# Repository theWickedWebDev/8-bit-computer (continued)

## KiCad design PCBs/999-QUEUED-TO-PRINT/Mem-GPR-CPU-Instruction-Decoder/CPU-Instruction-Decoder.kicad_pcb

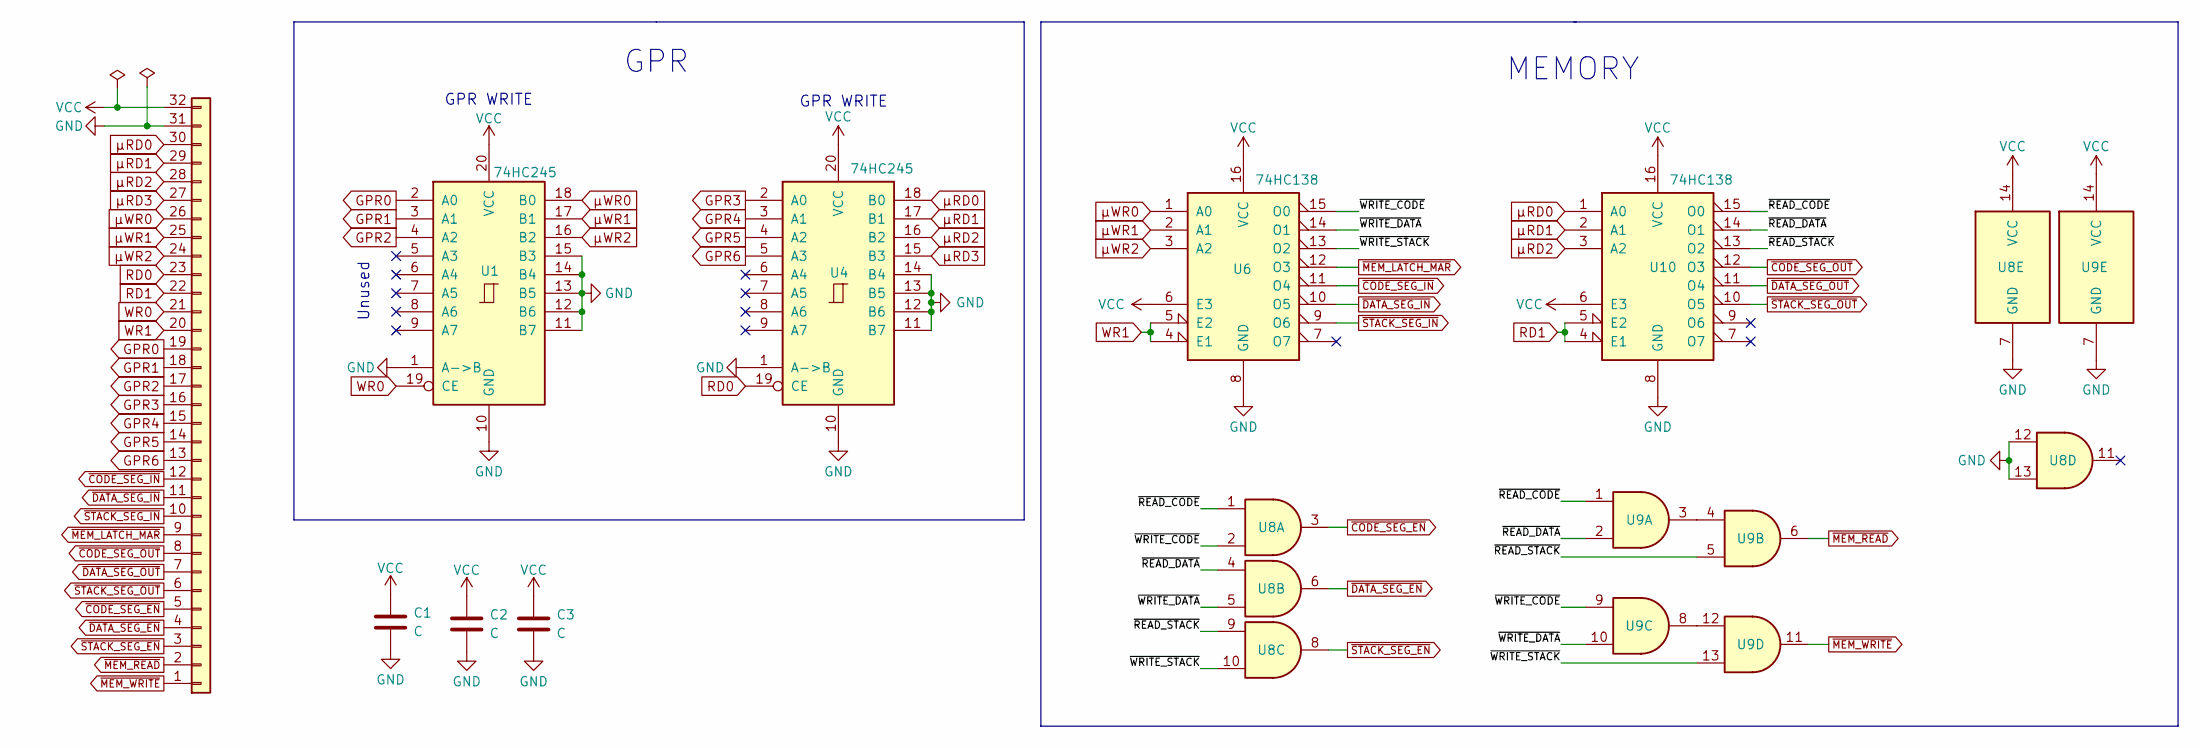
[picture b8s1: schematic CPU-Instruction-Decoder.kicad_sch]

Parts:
C1, C2, C3: C; C_0805_2012Metric
J1: Conn_01x32; PinHeader_1x32_P2.54mm_Horizontal
U1, U4: 74HC245; SOIC-20W_7.5x12.8mm_P1.27mm
U6, U10: 74HC138; SOIC-16_3.9x9.9mm_P1.27mm
U8, U9: 74HC08; SOIC-14_3.9x8.7mm_P1.27mm

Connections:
/~READ_CODE: U8.1, U9.1, U10.15 (O0)
/~READ_DATA: U8.4, U9.2, U10.14 (O1)
/~READ_STACK: U8.9, U9.5, U10.13 (O2)
/~WRITE_CODE: U6.15 (O0), U8.2, U9.9
/~WRITE_DATA: U6.14 (O1), U8.5, U9.10
/~WRITE_STACK: U6.13 (O2), U8.10, U9.13
GND: C1.2, C2.2, C3.2, J1.31, U1.1 (A->B), U1.10 (GND), U1.11 (B7), U1.12 (B6), U1.13 (B5), U1.14 (B4), U1.15 (B3), U4.1 (A->B), U4.10 (GND), U4.11 (B7), U4.12 (B6), U4.13 (B5), U4.14 (B4), U6.8 (GND), U8.7 (GND), U8.12, U8.13, U9.7 (GND), U10.8 (GND)
GPR0: J1.19, U1.2 (A0)
GPR1: J1.18, U1.3 (A1)
GPR2: J1.17, U1.4 (A2)
GPR3: J1.16, U4.2 (A0)
GPR4: J1.15, U4.3 (A1)
GPR5: J1.14, U4.4 (A2)
GPR6: J1.13, U4.5 (A3)
unnamed: U9.3, U9.4
unnamed: U9.8, U9.12
RD0: J1.23, U4.19 (CE)
RD1: J1.22, U10.4 (E1), U10.5 (E2)
VCC: C1.1, C2.1, C3.1, J1.32, U1.20 (VCC), U4.20 (VCC), U6.6 (E3), U6.16 (VCC), U8.14 (VCC), U9.14 (VCC), U10.6 (E3), U10.16 (VCC)
WR0: J1.21, U1.19 (CE)
WR1: J1.20, U6.4 (E1), U6.5 (E2)
~CODE_SEG_EN: J1.5, U8.3
~CODE_SEG_IN: J1.12, U6.11 (O4)
~CODE_SEG_OUT: J1.8, U10.12 (O3)
~DATA_SEG_EN: J1.4, U8.6
~DATA_SEG_IN: J1.11, U6.10 (O5)
~DATA_SEG_OUT: J1.7, U10.11 (O4)
~MEM_LATCH_MAR: J1.9, U6.12 (O3)
~MEM_READ: J1.2, U9.6
~MEM_WRITE: J1.1, U9.11
~STACK_SEG_EN: J1.3, U8.8
~STACK_SEG_IN: J1.10, U6.9 (O6)
~STACK_SEG_OUT: J1.6, U10.10 (O5)
μRD0: J1.30, U4.18 (B0), U10.1 (A0)
μRD1: J1.29, U4.17 (B1), U10.2 (A1)
μRD2: J1.28, U4.16 (B2), U10.3 (A2)
μRD3: J1.27, U4.15 (B3)
μWR0: J1.26, U1.18 (B0), U6.1 (A0)
μWR1: J1.25, U1.17 (B1), U6.2 (A1)
μWR2: J1.24, U1.16 (B2), U6.3 (A2)

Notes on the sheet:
MEMORY
GPR
GPR WRITE
Unused

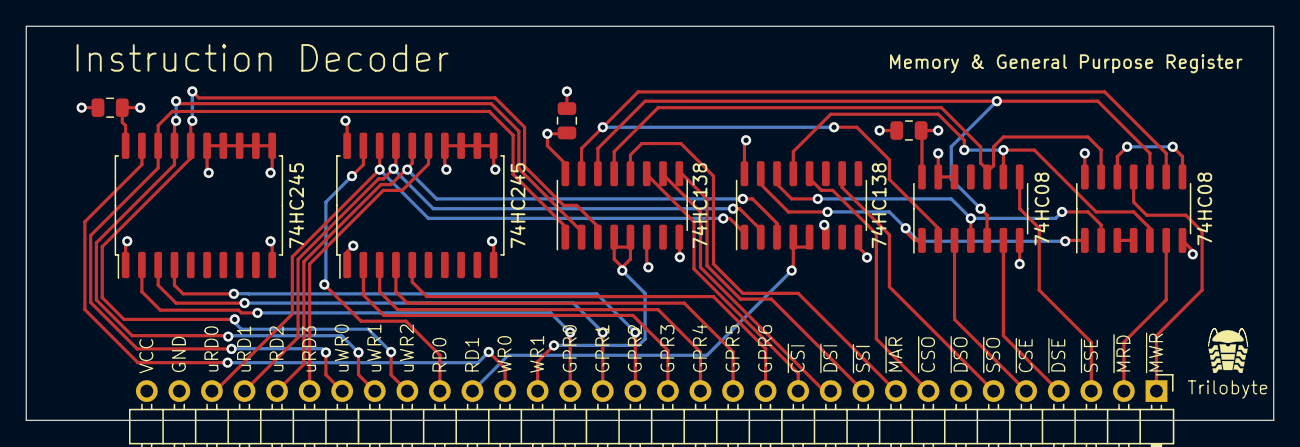
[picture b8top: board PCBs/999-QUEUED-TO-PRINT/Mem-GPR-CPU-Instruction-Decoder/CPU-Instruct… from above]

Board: 4 copper layers, 97.3 x 30.7 mm, 10 parts (0 on the bottom side), 40 nets.

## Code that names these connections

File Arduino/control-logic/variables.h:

#define CPU_CLOCK 12

#define SHIFT_DATA 2
#define SHIFT_CLK 3
#define SHIFT_LATCH 4
#define SHIFT_OE 5

#define BUS_BUFFER_OE 10
#define BUS_BUFFER_DIR_PIN 11

#define BUS0 14
#define BUS1 15
#define BUS2 16
#define BUS3 17
#define BUS4 18
#define BUS5 19
#define BUS6 20
#define BUS7 21


long addressBus = 0x0000;
long dataBus = 0x00;
byte bus = 0x0;

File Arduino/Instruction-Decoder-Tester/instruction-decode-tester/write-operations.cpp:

#define SPR_WR_GROUP    0x3 << 4
#define JCC_WR_GROUP    0x2 << 4
#define MEM_WR_GROUP    0x1 << 4
#define GPR_WR_GROUP    0x0 << 4

// Special Pin
#define INC_PC          0b1 << 7

// CONTROL GROUP 3 (0bx000xxxx)
#define SP_DEC          SPR_WR_GROUP | 0x0
#define SP_INC          SPR_WR_GROUP | 0x1
#define SP_IN           SPR_WR_GROUP | 0x2
#define INST_IN         SPR_WR_GROUP | 0x3
#define A_IN            SPR_WR_GROUP | 0x4
#define B_IN            SPR_WR_GROUP | 0x5
#define PC_DEC          SPR_WR_GROUP | 0x6
// #define FREE         SPR_WR_GROUP | 0x7
// #define FREE         SPR_WR_GROUP | 0x8
#define FLG_IN          SPR_WR_GROUP | 0x9
#define FLG_RESTORE     SPR_WR_GROUP | 0xA
// #define FREE    SPR_WR_GROUP | 0xB .. 0xF

// CONTROL GROUP 2 (0bx001xxxx)
#define JP              JCC_WR_GROUP | 0x0
#define JLE_JNG         JCC_WR_GROUP | 0x1
#define JG_JNLE         JCC_WR_GROUP | 0x2
#define JGE_JNL         JCC_WR_GROUP | 0x3
#define JL_JNGE         JCC_WR_GROUP | 0x4
#define JA_JNBE         JCC_WR_GROUP | 0x5
#define JBE_JNA         JCC_WR_GROUP | 0x6
#define JNB_JAE_JNC     JCC_WR_GROUP | 0x7
#define JB_JNAE_JC      JCC_WR_GROUP | 0x8
#define JNE_JNZ         JCC_WR_GROUP | 0x9
#define JE_JZ           JCC_WR_GROUP | 0xA
#define JNS             JCC_WR_GROUP | 0xB
#define JS              JCC_WR_GROUP | 0xC
#define JNO             JCC_WR_GROUP | 0xD
#define JO              JCC_WR_GROUP | 0xE

// CONTROL GROUP 1 (0bx010xxxx)
#define MEM_CODE_IN     MEM_WR_GROUP | 0x0
#define MEM_DATA_IN     MEM_WR_GROUP | 0x1
#define MEM_STACK_IN    MEM_WR_GROUP | 0x2
#define MAR_IN          MEM_WR_GROUP | 0x3
#define CODE_SEG_IN     MEM_WR_GROUP | 0x4
#define DATA_SEG_IN     MEM_WR_GROUP | 0x5
#define STACK_SEG_IN    MEM_WR_GROUP | 0x6
// #define FREE    MEM_WR_GROUP | 0x7

// CONTROL GROUP 0 (0bx011xxxx)
#define NOP             GPR_WR_GROUP | 0x0
#define C_IN            GPR_WR_GROUP | 0x1
#define D_IN            GPR_WR_GROUP | 0x2
#define S1_IN           GPR_WR_GROUP | 0x3
#define S2_IN           GPR_WR_GROUP | 0x4
#define F               GPR_WR_GROUP | 0x5
#define S3_IN           GPR_WR_GROUP | 0x6

// CONTROL GROUP 4 (0bx100xxxx) - Free Unused (up to 16 more control lines)
// CONTROL GROUP 5 (0bx101xxxx) - Free Unused (up to 16 more control lines)
// CONTROL GROUP 6 (0bx110xxxx) - Free Unused (up to 16 more control lines)
// CONTROL GROUP 7 (0bx111xxxx) - Free Unused (up to 16 more control lines)

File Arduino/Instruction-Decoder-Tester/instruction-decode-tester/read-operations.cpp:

#define SPR_GROUP_OUT           0x4 << 4
#define ALU_GROUP_OUT           0x3 << 4
#define NOT_ALU_GROUP_OUT       0x2 << 4
#define MEM_GROUP_OUT           0x1 << 4
#define GPR_GROUP_OUT           0x0 << 4

// Special Pin
#define RESET_SP                0b1 << 7

// CONTROL GROUP 4 (0bx000xxxx)
#define PC_OUT      SPR_GROUP_OUT | 0x0
#define SP_OUT      SPR_GROUP_OUT | 0x1
#define FLAG_OUT    SPR_GROUP_OUT | 0x2
// #define FREE     SPR_GROUP_OUT | 0x3 .. 0XF // FREE

// CONTROL GROUP 3 (0bx001xxxx)
#define A_OUT       ALU_GROUP_OUT | 0x0
#define ADD_OUT     ALU_GROUP_OUT | 0x1
#define ADC_OUT     ALU_GROUP_OUT | 0x2
#define SUB_OUT     ALU_GROUP_OUT | 0x3
#define SBB_OUT     ALU_GROUP_OUT | 0x4
#define INC_OUT     ALU_GROUP_OUT | 0x5
#define DEC_OUT     ALU_GROUP_OUT | 0x6
#define AND_OUT     ALU_GROUP_OUT | 0x7
#define OR_OUT      ALU_GROUP_OUT | 0x8
#define XOR_OUT     ALU_GROUP_OUT | 0x9
#define SHL_OUT     ALU_GROUP_OUT | 0xA
#define SHR_OUT     ALU_GROUP_OUT | 0xB
#define ASL_OUT     ALU_GROUP_OUT | 0xC
#define ASR_OUT     ALU_GROUP_OUT | 0xD
#define ROR_OUT     ALU_GROUP_OUT | 0xE
#define ROL_OUT     ALU_GROUP_OUT | 0xF

// CONTROL GROUP 2 (0bx010xxxx)
#define NOT_OUT     NOT_ALU_GROUP_OUT | 0x0
#define NADD_OUT    NOT_ALU_GROUP_OUT | 0x1
#define NADC_OUT    NOT_ALU_GROUP_OUT | 0x2
#define NSUB_OUT    NOT_ALU_GROUP_OUT | 0x3
#define NSBB_OUT    NOT_ALU_GROUP_OUT | 0x4
#define NINC_OUT    NOT_ALU_GROUP_OUT | 0x5
#define NDEC_OUT    NOT_ALU_GROUP_OUT | 0x6
#define NAND_OUT    NOT_ALU_GROUP_OUT | 0x7
#define NOR_OUT     NOT_ALU_GROUP_OUT | 0x8
#define XNOR_OUT    NOT_ALU_GROUP_OUT | 0x9
#define NSHL_OUT    NOT_ALU_GROUP_OUT | 0xA
#define NSHR_OUT    NOT_ALU_GROUP_OUT | 0xB
#define NASL_OUT    NOT_ALU_GROUP_OUT | 0xC
#define NASR_OUT    NOT_ALU_GROUP_OUT | 0xD
#define NROR_OUT    NOT_ALU_GROUP_OUT | 0xE
#define NROL_OUT    NOT_ALU_GROUP_OUT | 0xF

// CONTROL GROUP 1 (0bx011xxxx)
#define MEM_CODE_OUT        MEM_GROUP_OUT | 0x0
#define MEM_DATA_OUT        MEM_GROUP_OUT | 0x1
#define MEM_STACK_OUT       MEM_GROUP_OUT | 0x2
#define CODE_SEG_OUT        MEM_GROUP_OUT | 0x3
#define DATA_SEG_OUT        MEM_GROUP_OUT | 0x4
#define STACK_SEG_OUT       MEM_GROUP_OUT | 0x5
// #define MEM_OUT_UNUSED_6    MEM_GROUP_OUT | 0x6
// #define MEM_OUT_UNUSED_6    MEM_GROUP_OUT | 0x7

// CONTROL GROUP 0 (0bx100xxxx)
#define NOP                 GPR_GROUP_OUT | 0x0
#define C_OUT               GPR_GROUP_OUT | 0x1
#define D_OUT               GPR_GROUP_OUT | 0x2
#define S1_OUT              GPR_GROUP_OUT | 0x3
#define S2_OUT              GPR_GROUP_OUT | 0x4
#define S1S2_OUT            GPR_GROUP_OUT | 0x5
#define F_OUT               GPR_GROUP_OUT | 0x6
#define S3_OUT              GPR_GROUP_OUT | 0x7
#define S3_LSB              GPR_GROUP_OUT | 0x8
#define S3_MSB              GPR_GROUP_OUT | 0x9

// CONTROL GROUP 5 (0bx101xxxx) - Free Unused (up to 16 more control lines)
// CONTROL GROUP 6 (0bx110xxxx) - Free Unused (up to 16 more control lines)
// CONTROL GROUP 7 (0bx111xxxx) - Free Unused (up to 16 more control lines)

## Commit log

2021-04-21 Added bunch of modules
2021-04-21 Screenshots added
2021-04-21 Added README
2021-04-22 Added RAM Modle
2021-04-22 Working on Display
2021-04-22 Updating README
2021-04-22 Added Bus Board
2021-04-23 Bus Board work
2021-04-23 Added control logic and library
2021-04-23 README updates
2021-04-23 Storage Registers added
2021-04-27 Added Register
2021-04-27 Updating Counter
2021-04-29 More Additions, Counter, ALU, Clock
2021-04-29 Added clock image
2021-04-29 Added Add/Sub Module
2021-04-29 BiDirectional Shift Register component
2021-05-02 Adding Programmable RAM Module
2021-05-08 Updated Control Unit
2021-05-08 Added RAM Programmer module
2021-05-08 Adding Clock 555 Module
2021-05-08 Adding Power Module
2021-05-08 Adding fun sound board module test
2021-05-08 Links for Help
2021-05-08 Updating Counter image
2021-05-10 Updated ADD/SUB module
2021-05-10 Added ALU Simplified Module
2021-05-10 Updating ALU 181
2021-05-10 Moving ALU directory
2021-05-10 Archiving old/obsolete modules - keeping for reference
2021-05-10 Updating READMEs
2021-05-18 Deletions
2021-05-18 RAM Memory Address Register
2021-05-18 Adding Control Logic Module
2021-05-18 Updating/Adding Kicad Libraries
2021-05-18 Adding some Sound module files
2021-05-18 Adding Fritzing breadboard for Sound module
2021-05-20 Adding Single Storage Register
2021-05-20 General update
2021-05-22 Updated to Control Logic board
2021-05-22 Updating RAM boards
2021-05-22 Updating RAM Programmer
2021-05-22 Updating RAM Readme
2021-05-22 Updating names
2021-05-22 Updating structure and readmes
2021-05-25 Updating Sound Module
2021-05-25 Updated Display Module
2021-05-25 Updated sound module readme
2021-05-26 FIX: Clock Switch Error on Ground
2021-05-26 Work on Sound Module
2021-05-30 Adding Multiplexer Module
2021-05-30 Updating Clock Module
2021-05-30 Adding start of Sound Controller
2021-06-15 Updating components
2021-06-15 [Final] Clock Module
2021-06-15 Added Fritzing Clock Module
2021-06-15 [Final] Storage Register
2021-06-15 Moving directories
2021-06-15 [Final] Counter Module
2021-06-15 Update Directories
2021-06-15 Added Fritzing file for Register
2021-06-17 [Added] ALU w/ registers module
2021-06-17 [RAM] Adding combined RAM modules
2021-06-17 [ALU] Updating ALU directory
2021-06-17 Moving more files around
2021-06-17 [RAM] Added gerber files
2021-06-17 [Display] Adding first pass display module
2021-06-18 [Display] Semi-final Display Module
2021-06-29 [Display Module] Updates after receiving PCB
2021-06-29 [RAM Module] Updates after receiving PCB
2021-06-29 [General] Updates
2021-06-29 [Ram Module] Added Schematic PNG and PDF
2021-07-04 [Code] Compiler for Microcode
2021-07-04 [Libraries] Updating Libaries
2021-07-04 [ALU] Updated ALU - needs work
2021-07-04 [Full] Temp, WIP
2021-07-04 [SMD] Working on SMD boards
2021-07-04 [Counter] Updates after printing
2021-07-04 [Micocode] Updating Control - WIP
2021-07-04 cache
2021-07-10 Saving
2021-09-09 ARCHIVING
2021-09-10 Added SMD Modules
2021-11-19 whole hell update
2021-11-28 biggggg update and react app
2021-11-28 Renamed directories
2021-11-28 GH Pages setup
2021-11-28 Updating
2021-11-28 Set theme jekyll-theme-minimal
2021-11-28 updated webapp
2021-11-28 Added more to webapp
2021-12-09 large save haahh
2022-01-15 Major Update
2022-01-18 Documentation and Cleanup
2022-02-28 STUPID UPDATE MAJOR SAVE
2022-04-18 Major Cleanup - Apr, 18 2022
2022-08-27 cray cray save
2022-08-27 Microcode work
2022-11-09 save
